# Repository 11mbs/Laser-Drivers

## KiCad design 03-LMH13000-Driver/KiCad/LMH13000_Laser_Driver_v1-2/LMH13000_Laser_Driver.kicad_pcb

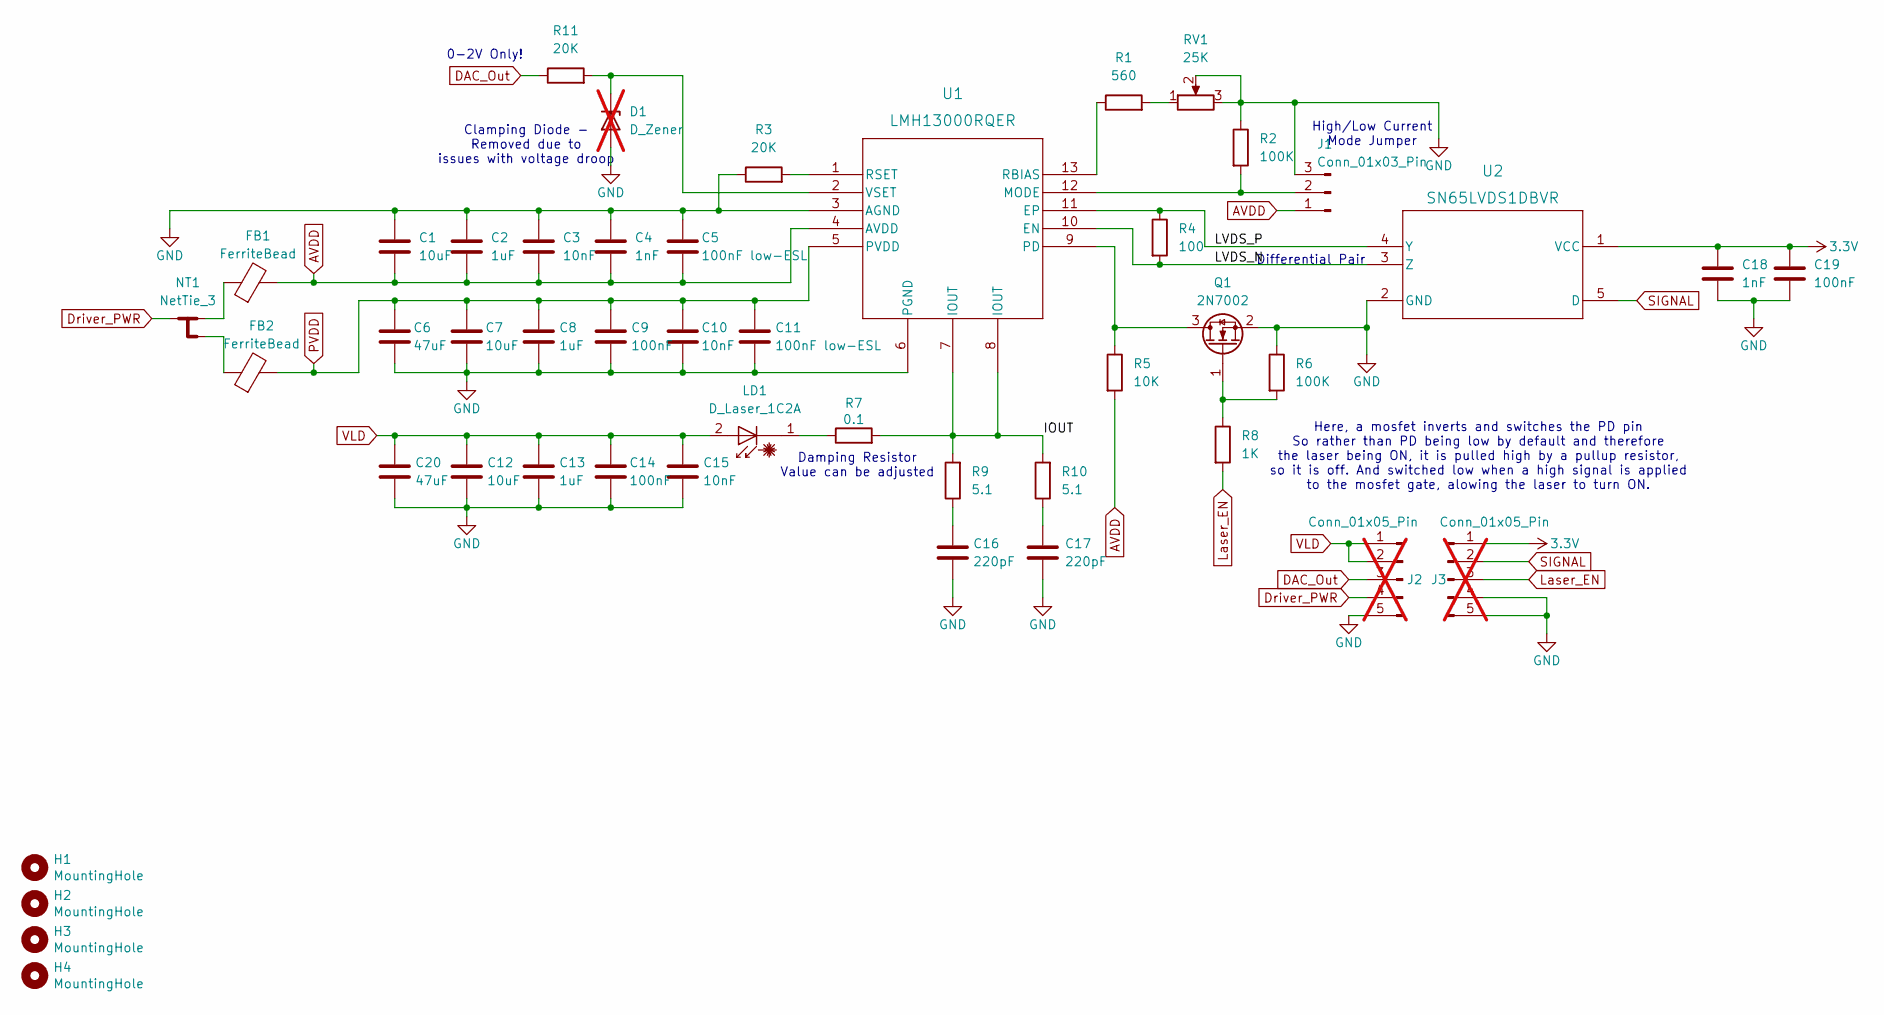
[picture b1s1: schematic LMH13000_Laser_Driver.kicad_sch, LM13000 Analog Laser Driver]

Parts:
C1, C7, C12: 10uF; C_0805_2012Metric
C2, C8, C13: 1uF; C_0603_1608Metric
C3, C10, C15: 10nF; C_0402_1005Metric
C4, C18: 1nF; C_0402_1005Metric
C5, C11: 100nF low-ESL; C_0402_1005Metric
C6, C20: 47uF; C_1206_3216Metric
C9, C14, C19: 100nF; C_0402_1005Metric
C16, C17: 220pF; C_0402_1005Metric
D1: D_Zener; D_SOD-523; LCSC Part C2760566; not fitted
FB1, FB2: FerriteBead; L_0805_2012Metric; LCSC Part C16903
H1, H2, H3, H4: MountingHole; MountingHole_3.2mm_M3
J1: Conn_01x03_Pin; PinHeader_1x03_P2.54mm_Vertical; LCSC Part C42431836
J2, J3: Conn_01x05_Pin; PinHeader_1x05_P2.54mm_Vertical; LCSC Part C42431835; not fitted
LD1: D_Laser_1C2A; JST_XH_B2B-XH-A_1x02_P2.50mm_Vertical; LCSC Part C495685
NT1: NetTie_3; NetTie-3_SMD_Pad0.5mm
Q1: 2N7002; SOT-23; LCSC Part C124475
R1: 560; R_0805_2012Metric
R2: 100K; R_0402_1005Metric
R3, R11: 20K; R_0603_1608Metric
R4: 100; R_0402_1005Metric
R5: 10K; R_0402_1005Metric
R6: 100K; R_0603_1608Metric
R7: 0.1; R_2512_6332Metric_Pad1.40x3.35mm_HandSolder; LCSC Part C49164916
R8: 1K; R_0603_1608Metric
R9, R10: 5.1; R_0402_1005Metric
RV1: 25K; Potentiometer_Bourns_3296W_Vertical; LCSC Part C55264
U1: LMH13000RQER; XLMH13000RQER.A_WQFN-HR_TXI_TEX; LCSC Part C48892016
U2: SN65LVDS1DBVR; DBV0005A_N; LCSC Part C465731

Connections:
3.3V: C18.1, C19.1, J3.1, U2.1 (VCC)
/IOUT: R7.2, R9.2, R10.2, U1.7 (IOUT), U1.8 (IOUT)
/LVDS_N: R4.2, U1.10 (EN), U2.3 (Z)
/LVDS_P: R4.1, U1.11 (EP), U2.4 (Y)
AVDD: C1.2, C2.2, C3.2, C4.2, C5.2, FB1.2, J1.1, R5.2, U1.4 (AVDD)
DAC_Out: J2.3, R11.1
Driver_PWR: J2.4, NT1.2
GND: C1.1, C2.1, C3.1, C4.1, C5.1, C6.2, C7.2, C8.2, C9.2, C10.2, C11.2, C12.2, C13.2, C14.2, C15.2, C16.2, C17.2, C18.2, C19.2, C20.2, D1.2 (A), J1.3, J2.5, J3.4, J3.5, Q1.2 (S), R2.1, R3.1, R6.1, RV1.2, RV1.3, U1.3 (AGND), U1.6 (PGND), U2.2 (GND)
Laser_EN: J3.3, R8.2
unnamed: C16.1, R9.1
unnamed: C17.1, R10.1
unnamed: D1.1 (K), R11.2, U1.2 (VSET)
unnamed: FB1.1, NT1.1
unnamed: FB2.1, NT1.3
unnamed: J1.2, R2.2, U1.12 (MODE)
unnamed: LD1.1 (K), R7.1
unnamed: Q1.3 (D), R5.1, U1.9 (PD)
unnamed: Q1.1 (G), R6.2, R8.1
unnamed: R1.2, RV1.1
unnamed: R1.1, U1.13 (RBIAS)
unnamed: R3.2, U1.1 (RSET)
PVDD: C6.1, C7.1, C8.1, C9.1, C10.1, C11.1, FB2.2, U1.5 (PVDD)
SIGNAL: J3.2, U2.5 (D)
VLD: C12.1, C13.1, C14.1, C15.1, C20.1, J2.1, J2.2, LD1.2 (A)

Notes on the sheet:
High/Low Current Mode Jumper
Clamping Diode - Removed due to issues with voltage droop
Differential Pair
Damping Resistor Value can be adjusted
Here, a mosfet inverts and switches the PD pin So rather than PD being low by default and therefore the laser being ON, it is pulled high by a pullup resistor, so it is off. And switched low when a high signal is applied to the mosfet gate, alowing the laser to turn ON.
0-2V Only!

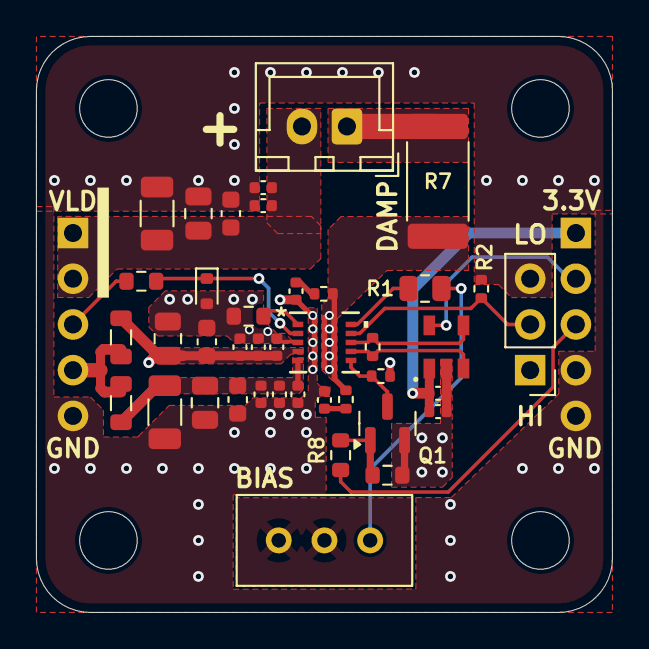
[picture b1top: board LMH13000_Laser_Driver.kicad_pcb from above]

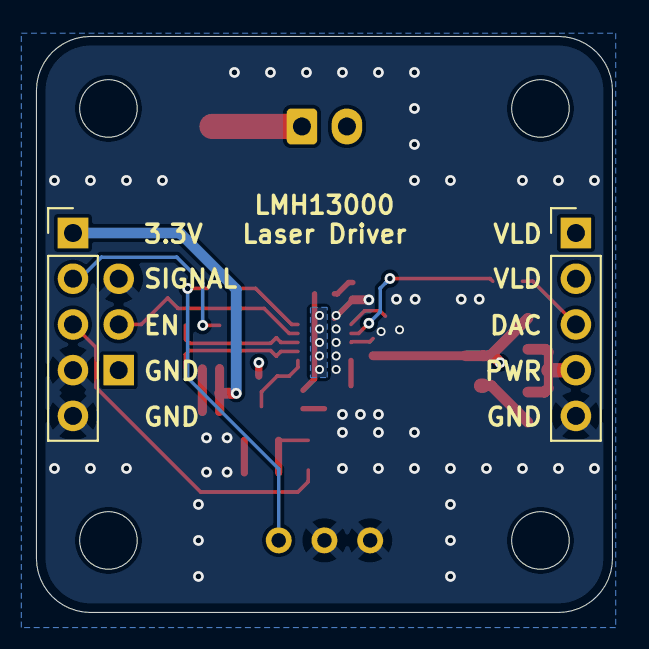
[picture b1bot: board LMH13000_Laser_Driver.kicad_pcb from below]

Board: 4 copper layers, 32.0 x 32.0 mm, 47 parts (2 on the bottom side), 24 nets.

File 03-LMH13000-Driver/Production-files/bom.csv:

Designator,Footprint,Quantity,Value,LCSC Part #
"C1, C12, C7",805,3,10uF,
"C10, C15, C3",402,3,10nF,
"C11, C5",402,2,100nF low-ESL,
"C13, C2, C8",603,3,1uF,
"C14, C19, C9",402,3,100nF,
"C16, C17",402,2,220pF,
"C18, C4",402,2,1nF,
"C20, C6",1206,2,47uF,
"FB1, FB2",805,2,FerriteBead,C16903
J1,PinHeader_1x03_P2.54mm_Vertical,1,Conn_01x03_Pin,C42431836
LD1,JST_XH_B2B-XH-A_1x02_P2.50mm_Vertical,1,D_Laser_1C2A,C495685
Q1,SOT-23,1,2N7002,C124475
R1,805,1,560,
"R10, R9",402,2,5.1,
"R11, R3",603,2,20K,
R2,402,1,100K,
R4,402,1,100,
R5,402,1,10K,
R6,603,1,100K,
R7,2512,1,0.1,C49164916
R8,603,1,1K,
RV1,Potentiometer_Bourns_3296W_Vertical,1,25K,C55264
U1,XLMH13000RQER.A_WQFN-HR_TXI_TEX,1,LMH13000RQER,C48892016
U2,DBV0005A_N,1,SN65LVDS1DBVR,C465731
